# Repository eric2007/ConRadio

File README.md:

# ConRadio
a portable wide-frequency radio based on SAF7730 and TEF6730

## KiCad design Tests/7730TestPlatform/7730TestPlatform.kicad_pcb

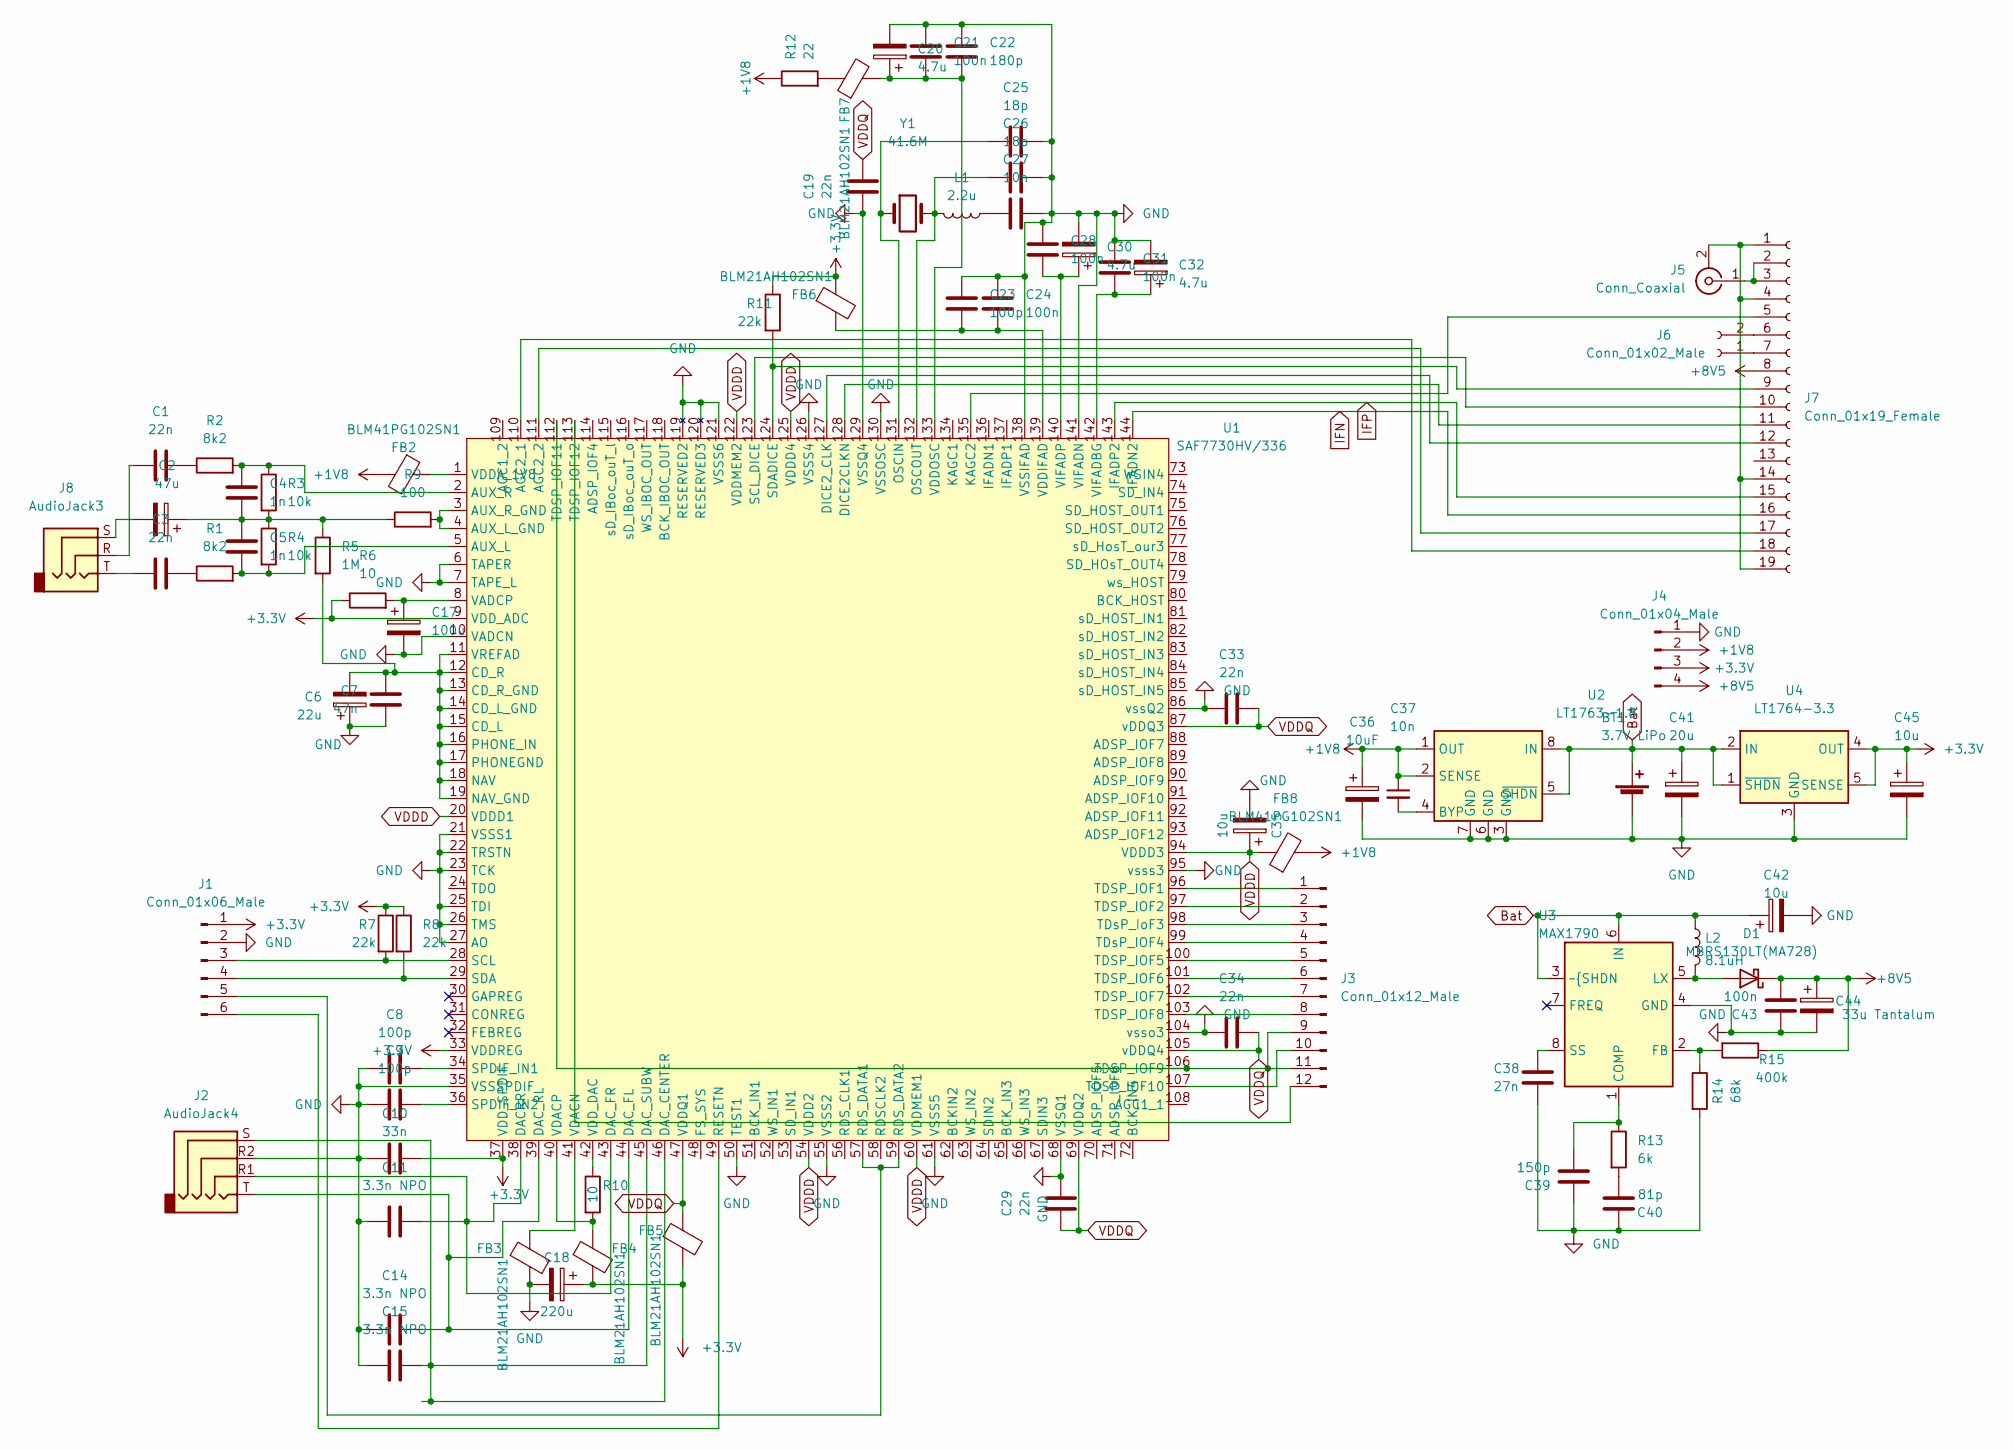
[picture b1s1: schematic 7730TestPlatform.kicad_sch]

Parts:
BT1: 3.7V LiPo; Molex_KK-254_AE-6410-02A_1x02_P2.54mm_Vertical
C1, C3, C19, C29, C33, C34: 22n; C_0603_1608Metric_Pad1.08x0.95mm_HandSolder
C2: 47u; CP_Elec_4x5.4
C4, C5: 1n; C_0603_1608Metric_Pad1.08x0.95mm_HandSolder
C6: 22u; CP_Elec_4x5.4
C7: 47n; C_0603_1608Metric_Pad1.08x0.95mm_HandSolder
C8, C9, C23: 100p; C_0603_1608Metric_Pad1.08x0.95mm_HandSolder
C10: 33n; C_0603_1608Metric_Pad1.08x0.95mm_HandSolder
C11, C14, C15: 3.3n NPO; C_0603_1608Metric_Pad1.08x0.95mm_HandSolder
C17: 100u; CP_Elec_6.3x5.4_Nichicon
C18: 220u; CP_Elec_10x10
C20, C30, C32: 4.7u; CP_Elec_4x5.4
C21, C24, C28, C31, C43: 100n; C_0603_1608Metric_Pad1.08x0.95mm_HandSolder
C22: 180p; C_0603_1608Metric_Pad1.08x0.95mm_HandSolder
C25, C26: 18p; C_0603_1608Metric_Pad1.08x0.95mm_HandSolder
C27, C37: 10n; C_0603_1608Metric_Pad1.08x0.95mm_HandSolder
C35, C42, C45: 10u; CP_Elec_4x5.4
C36: 10uF; CP_Elec_4x5.4
C38: 27n; C_0603_1608Metric_Pad1.08x0.95mm_HandSolder
C39: 150p; C_0603_1608Metric_Pad1.08x0.95mm_HandSolder
C40: 81p; C_0603_1608Metric_Pad1.08x0.95mm_HandSolder
C41: 20u; CP_Elec_4x5.4
C44: 33u Tantalum; CP_EIA-3528-21_Kemet-B_Pad1.50x2.35mm_HandSolder
D1: MBRS130LT(MA728); D_SOD-323_HandSoldering
FB2, FB8: BLM41PG102SN1; L_1806_4516Metric_Pad1.45x1.90mm_HandSolder
FB3, FB4, FB5, FB6, FB7: BLM21AH102SN1; L_0805_2012Metric_Pad1.15x1.40mm_HandSolder
J1: Conn_01x06_Male; PinHeader_1x06_P2.54mm_Vertical
J2: AudioJack4; Jack_3.5mm_PJ320D_Horizontal
J3: Conn_01x12_Male; PinHeader_1x12_P2.54mm_Vertical
J4: Conn_01x04_Male; PinHeader_1x04_P2.54mm_Vertical
J5: Conn_Coaxial; SMA_Amphenol_901-143_Horizontal
J6: Conn_01x02_Male; PinHeader_1x02_P2.54mm_Vertical
J7: Conn_01x19_Female; PinSocket_1x19_P2.54mm_Vertical
J8: AudioJack3; Jack_3.5mm_CUI_SJ1-3533NG_Horizontal
L1: 2.2u; L_0805_2012Metric_Pad1.15x1.40mm_HandSolder
L2: 8.1uH; L_Taiyo-Yuden_MD-4040
R1, R2: 8k2; R_0603_1608Metric_Pad0.98x0.95mm_HandSolder
R3, R4: 10k; R_0603_1608Metric_Pad0.98x0.95mm_HandSolder
R5: 1M; R_0603_1608Metric_Pad0.98x0.95mm_HandSolder
R6, R10: 10; R_0603_1608Metric_Pad0.98x0.95mm_HandSolder
R7, R8, R11: 22k; R_0603_1608Metric_Pad0.98x0.95mm_HandSolder
R9: 100; R_0603_1608Metric_Pad0.98x0.95mm_HandSolder
R12: 22; R_0603_1608Metric_Pad0.98x0.95mm_HandSolder
R13: 6k; R_0603_1608Metric_Pad0.98x0.95mm_HandSolder
R14: 68k; R_0603_1608Metric_Pad0.98x0.95mm_HandSolder
R15: 400k; R_0603_1608Metric_Pad0.98x0.95mm_HandSolder
U1: SAF7730HV/336; LQFP-144_20x20mm_P0.5mm
U2: LT1763-1.8; SO-8_3.9x4.9mm_P1.27mm
U3: MAX1790; max1790eua
U4: LT1764-3.3; TO-263-5_TabPin3
Y1: 41.6M; Crystal_SMD_5032-2Pin_5.0x3.2mm_HandSoldering

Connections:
+1V8: C36.1, C37.1, FB2.2, FB8.2, J4.2, R12.1, U2.1 (OUT), U2.2 (SENSE)
+3V3: C10.2, C18.1, C45.1, FB4.2, FB5.2, FB6.1, J1.1, J4.3, R6.1, R7.1, R8.1, R11.1, U1.9 (VDD_ADC), U1.33 (VDDREG), U1.37 (VDD_SPDIF), U4.4 (OUT), U4.5 (SENSE)
+8V5: C43.1, C44.1, D1.1 (K), J4.4, J7.8, R15.1
Bat: BT1.1 (+), C41.1, C42.1, L2.1, U2.5 (~SHDN), U2.8 (IN), U3.3 (~{SHDN), U3.6 (IN), U4.1 (~SHDN), U4.2 (IN)
GND: BT1.2 (-), C6.1, C7.2, C8.1, C9.1, C10.1, C11.1, C14.1, C15.1, C17.2, C18.2, C19.1, C20.2, C21.1, C22.1, C23.1, C24.1, C25.2, C26.1, C27.2, C28.1, C29.1, C30.2, C31.1, C32.2, C33.1, C34.1, C35.2, C36.2, C38.1, C39.2, C40.2, C41.2, C42.2, C43.2, C44.2, C45.2, FB3.1, J1.2, J2.R2, J4.1, R14.2, U1.6 (TAPER), U1.7 (TAPE_L), U1.10 (VADCN), U1.21 (VSSS1), U1.22 (TRSTN), U1.23 (TCK), U1.25 (TDI), U1.26 (TMS), U1.27 (AO), U1.35 (VSSSPDIF), U1.50 (TEST1), U1.55 (VSSS2), U1.61 (VSSS5), U1.68 (VSSQ1), U1.86 (vssQ2), U1.95 (vsss3), U1.104 (vsso3), U1.119 (RESERVED2), U1.120 (RESERVED3), U1.121 (VSSS6), U1.126 (VSSS4), U1.129 (VSSQ4), U1.130 (VSSOSC), U1.138 (VSSIFAD), U1.141 (VIFADN), U2.3 (GND), U2.6 (GND), U2.7 (GND), U3.4 (GND), U4.3 (GND)
IFN: J7.16, U1.144 (IFADN2)
IFP: J7.15, U1.143 (IFADP2)
unnamed: C1.1, J8.R
unnamed: C1.2, R2.1
unnamed: C2.1, C4.2, C5.1, R3.2, R4.1, R5.1, R9.1
unnamed: C2.2, J8.S
unnamed: C3.1, J8.T
unnamed: C3.2, R1.1
unnamed: C4.1, R2.2, R3.1, U1.2 (AUX_R)
unnamed: C5.2, R1.2, R4.2, U1.5 (AUX_L)
unnamed: C6.2, C7.1, R5.2, U1.11 (VREFAD), U1.12 (CD_R), U1.13 (CD_R_GND), U1.14 (CD_L_GND), U1.15 (CD_L), U1.16 (PHONE_IN), U1.17 (PHONEGND), U1.18 (NAV), U1.19 (NAV_GND)
unnamed: C8.2, U1.34 (SPDIF_IN1)
unnamed: C9.2, U1.36 (SPDIF_IN2)
unnamed: C11.2, J2.R1, U1.38 (DACRR), U1.43 (DAC_FR)
unnamed: C14.2, J2.T, U1.39 (DAC_RL), U1.44 (DAC_FL)
unnamed: C15.2, J2.S, U1.45 (DAC_SUBW), U1.46 (DAC_CENTER)
unnamed: C17.1, R6.2, U1.8 (VADCP)
unnamed: C20.1, C21.2, C22.2, FB7.2, U1.133 (VDDOSC)
unnamed: C23.2, C24.2, FB6.2, U1.139 (VDDIFAD)
unnamed: C25.1, U1.131 (OSCIN), Y1.1
unnamed: C26.2, L1.2, U1.132 (OSCOUT), Y1.2
unnamed: C27.1, L1.1
unnamed: C28.2, C30.1, U1.140 (VIFADP)
unnamed: C31.2, C32.1, U1.142 (VIFADBG)
unnamed: C37.2, U2.4 (BYP)
unnamed: C38.2, U3.8 (SS)
unnamed: C39.1, R13.1, U3.1 (COMP)
unnamed: C40.1, R13.2
unnamed: D1.2 (A), L2.2, U3.5 (LX)
unnamed: FB2.1, U1.1 (VDDA_1V8)
unnamed: FB3.2, U1.41 (VDACN)
unnamed: FB4.1, R10.2, U1.40 (VDACP)
unnamed: FB7.1, R12.2
unnamed: J1.3, R7.2, U1.28 (SCL)
unnamed: J1.4, R8.2, U1.29 (SDA)
unnamed: J1.5, U1.57 (RDS_DATA1), U1.59 (RDS_DATA2)
unnamed: J1.6, U1.49 (RESETN)
unnamed: J3.1, U1.96 (TDSP_IOF1)
unnamed: J3.2, U1.97 (TDSP_IOF2)
unnamed: J3.3, U1.98 (TDsP_IoF3)
unnamed: J3.4, U1.99 (TDsP_IOF4)
unnamed: J3.5, U1.100 (TDSP_IOF5)
unnamed: J3.6, U1.101 (TDSP_IOF6)
unnamed: J3.7, U1.102 (TDSP_IOF7)
unnamed: J3.8, U1.103 (TDSP_IOF8)
unnamed: J3.10, U1.107 (TDSP_IOF10)
unnamed: J3.9, J3.11, U1.106 (TDSP_IOF9), U1.112 (TDSP_IOF11)
unnamed: J3.12, U1.113 (TDSP_IOF12)
unnamed: J5.1 (In), J7.2, J7.3
unnamed: J5.2 (Ext), J7.1, J7.4, J7.14, J7.19
unnamed: J6.1, J7.7
unnamed: J6.2, J7.6
unnamed: J7.5, U1.135 (KAGC2)
unnamed: J7.9, R11.2, U1.124 (SDADICE)
unnamed: J7.10, U1.123 (SCL_DICE)
unnamed: J7.11, U1.128 (DICE2CLKN)
unnamed: J7.12, U1.127 (DICE2_CLK)
unnamed: J7.17, U1.111 (AGC2_2)
unnamed: J7.18, U1.110 (AGC2_1)
unnamed: R9.2, U1.3 (AUX_R_GND), U1.4 (AUX_L_GND)
unnamed: R10.1, U1.42 (VDD_DAC)
unnamed: R14.1, R15.2, U3.2 (FB)
VDDD: C35.1, FB8.1, U1.20 (VDDD1), U1.54 (VDDD2), U1.60 (VDDMEM1), U1.94 (VDDD3), U1.122 (VDDMEM2), U1.125 (VDDD4)
VDDQ: C19.2, C29.2, C33.2, C34.2, FB5.1, U1.47 (VDDQ1), U1.69 (VDDQ2), U1.87 (vDDQ3), U1.105 (vDDQ4)

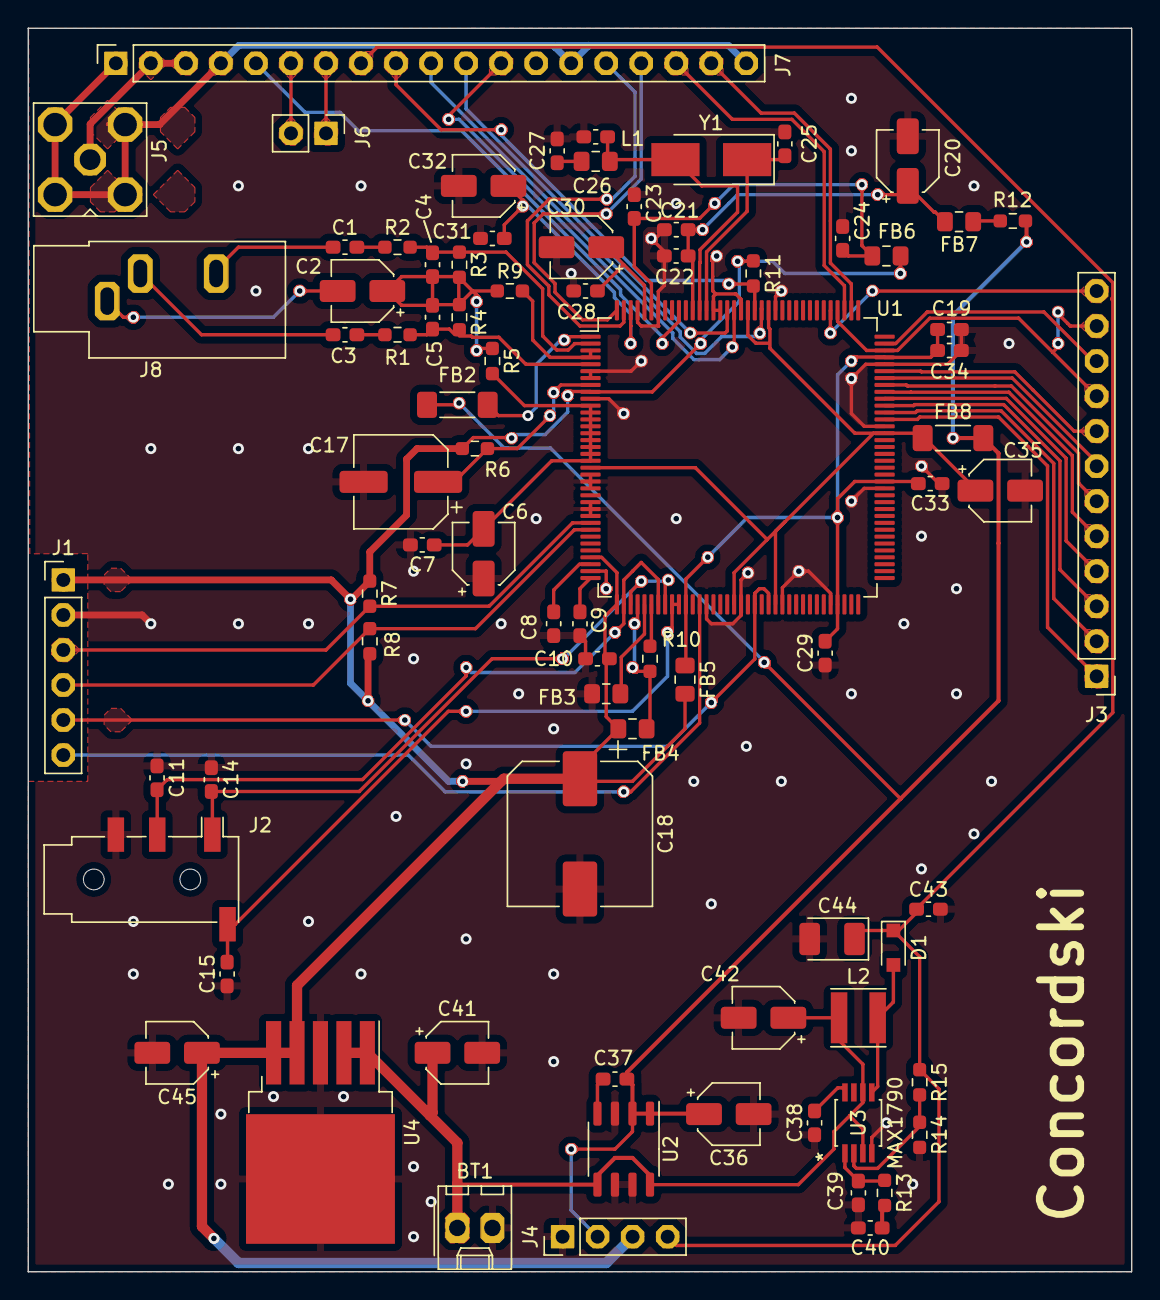
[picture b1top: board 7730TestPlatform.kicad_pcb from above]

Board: 2 copper layers, 80.0 x 90.2 mm, 81 parts (0 on the bottom side), 69 nets.

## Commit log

2022-06-28 Add Symbol SAF7730
2022-07-21 Finish SAF7730 routing
2022-07-31 Add power supply
2022-08-08 Finish Test Platform

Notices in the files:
parts and their libraries:
Copyright 2021 Accelerated Designs. All rights reserved.
